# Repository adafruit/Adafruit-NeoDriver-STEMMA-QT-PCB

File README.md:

## Adafruit NeoDriver - I2C to NeoPixel Driver Board - Stemma QT PCB

<a href="http://www.adafruit.com/products/5766"><br/>
Click here to purchase one from the Adafruit shop</a>

PCB files for the Adafruit NeoDriver - I2C to NeoPixel Driver Board - Stemma QT. 

Format is EagleCAD schematic and board layout
* https://www.adafruit.com/product/5766

### Description

NeoPixel LEDs (a.k.a WS2812 / SK6812 family) are a super-easy way to add addressable RGB lighting with only one GPIO. They're ubiquitous on microcontrollers, but some chips or single board computers (SBCs) don't have neopixel support due to the precision timing required to send data.

We often get folks asking how to get NeoPixels working on some OrangeBananaOnionRockchipAllWinner Pi type board, given we have our Blinka library that provides support for CircuitPython libraries including the NeoPixel library. But if theres no neopixel_write implementation written for that platform, it just wont work. And writing the neopixel-writer function is non-trivial on many chips: you really need fast GPIO and nanosecond-perfect timing.

A quick solution is this seesaw-based NeoDriver board here: send it the NeoPixel data you want to write over I2C and it will blit out the perfect pixel timing on the other side. We're using an ATtiny1616 so we have enough RAM to buffer a 512-pixel long strand. now, to be fair - its not super fast because we have to write each pixel over I2C, but with a 800KHz or 1MHz I2C clock and as long as you're not writing the whole strip at once, its not so bad!

We add a 5V charge-pump so even on 3V boards, you'll get a clean 5V signal. The pre-soldered terminal blocks and Stemma QT plugs make this a no-solder solution for adding NeoPixels easily to any device with I2C. The default I2C address is 0x60 but you can cut the bottom solder traces to change it to 0x60-0x67 inclusive.

Please note: To power NeoPixels you'll need about 10-30mA per pixel of clean 5V DC power, provided on the terminal blocks or you can just wire the 5V directly to the pixels if there's separate red and black power wires. There's no way the Stemma QT port can provide that much current so you can't just wire the pixels without an external power supply!

### License

Adafruit invests time and resources providing this open source design, please support Adafruit and open-source hardware by purchasing products from [Adafruit](https://www.adafruit.com)!

Designed by Limor Fried/Ladyada for Adafruit Industries.

Creative Commons Attribution/Share-Alike, all text above must be included in any redistribution. 
See license.txt for additional details.

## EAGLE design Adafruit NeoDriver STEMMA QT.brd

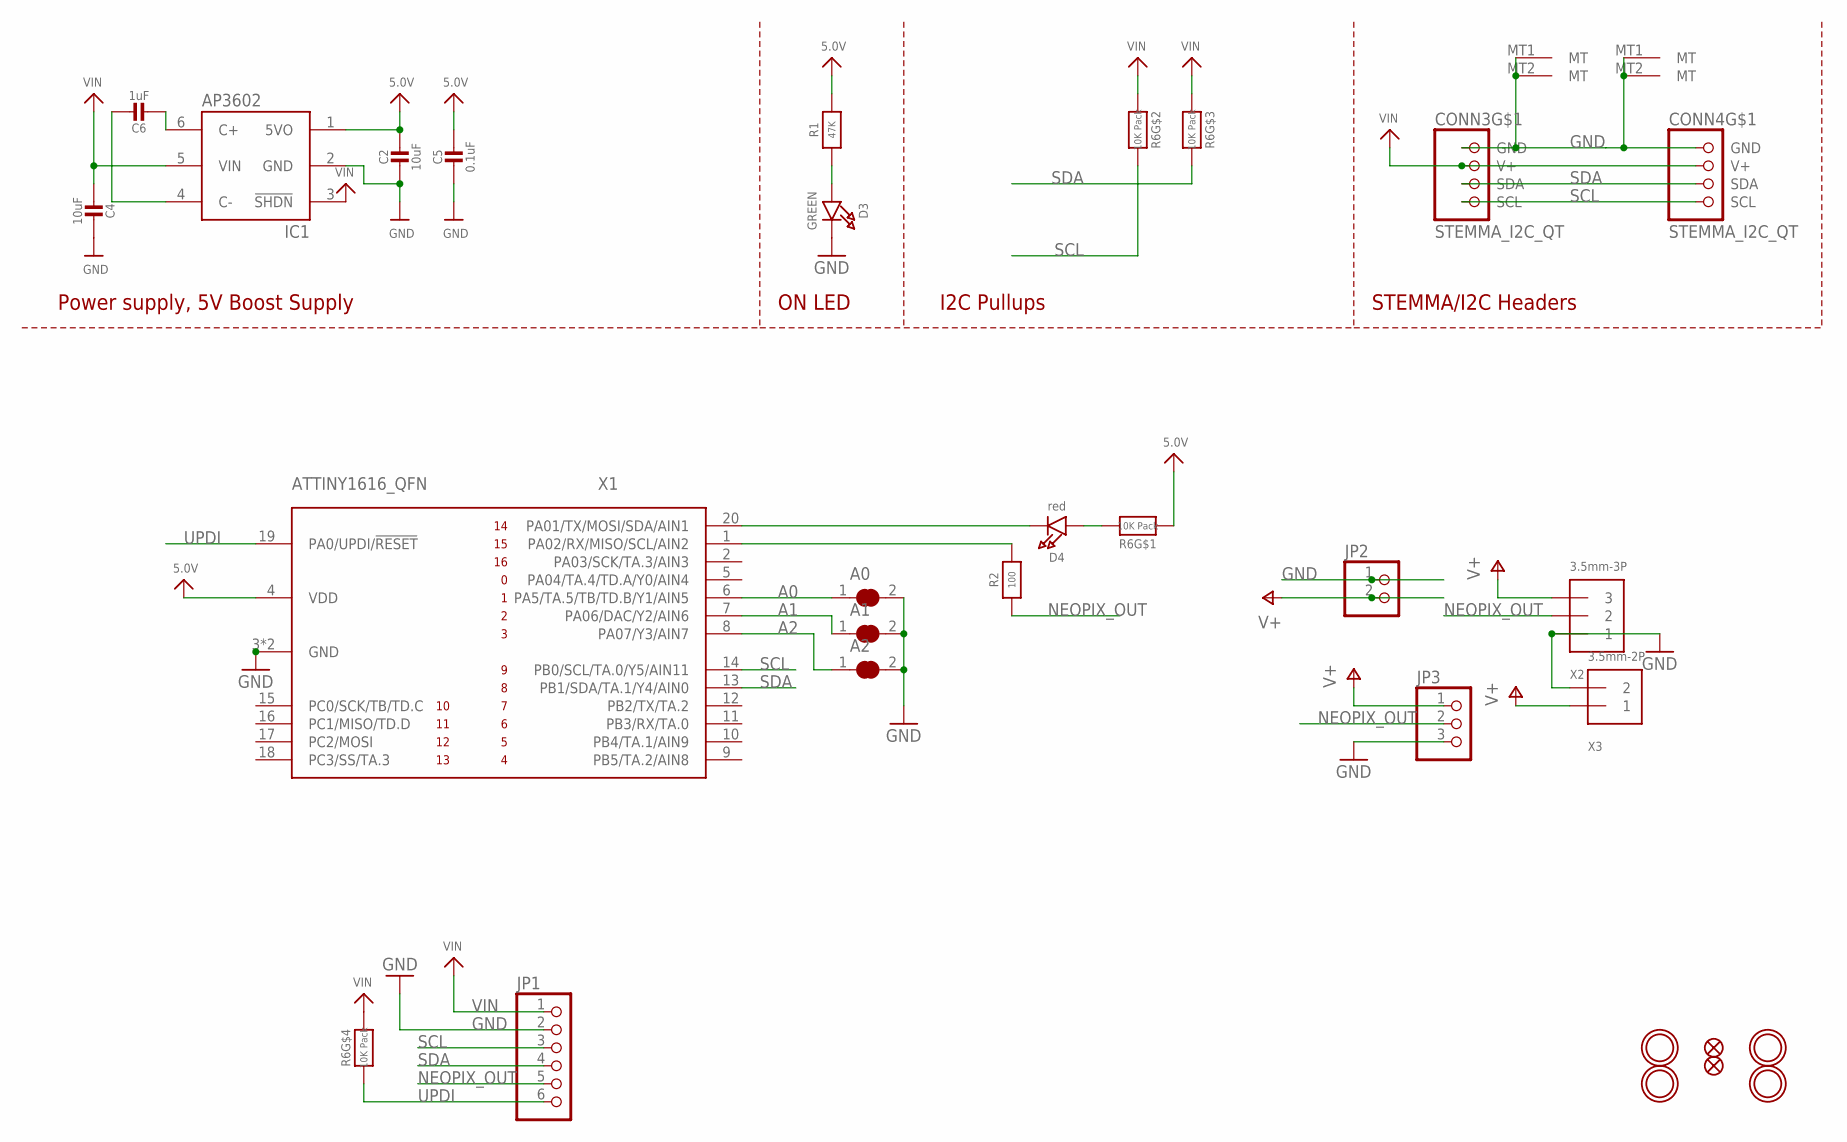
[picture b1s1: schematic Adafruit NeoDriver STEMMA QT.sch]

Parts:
A0, A1, A2: SOLDERJUMPER_CLOSED; SOLDERJUMPER_CLOSEDWIRE
C2, C4: 10uF; 0805-NO
C5: 0.1uF; 0603-NO
C6: 1uF; 0603-NO
CONN3, CONN4: STEMMA_I2C_QT; JST_SH4
D3: GREEN; CHIPLED_0603_NOOUTLINE
D4: red; CHIPLED_0603_NOOUTLINE
FID1, FID2: FIDUCIAL_1MM
IC1: AP3602; SOT23-6
JP1: HEADER-1X670MIL; 1X06_ROUND_70
JP2: HEADER-1X2ROUND; 1X02_ROUND
JP3: HEADER-1X3ROUND; 1X03_ROUND
R1: 47K; 0603-NO
R2: 100; 0603-NO
R6: 10K Pack; RESPACK_4X0603
U$1, U$6, U$9, U$18: MOUNTINGHOLE2.5; MOUNTINGHOLE_2.5_PLATED
X1: ATTINY1616_QFN; QFN20_3MM
X2: 3.5mm-3P; TERMBLOCK_1X3-3.5MM
X3: 3.5mm-2P; TERMBLOCK_1X2-3.5MM

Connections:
5.0V: C2.1, C5.1, IC1.1 (5VO), R1.2, R6.1, X1.4 (VDD)
A0: A0.1, X1.6 (PA5/TA.5/TB/TD.B/Y1/AIN5)
A1: A1.1, X1.7 (PA06/DAC/Y2/AIN6)
A2: A2.1, X1.8 (PA07/Y3/AIN7)
ACT: D4.C, X1.20 (PA01/TX/MOSI/SDA/AIN1)
GND: A0.2, A1.2, A2.2, C2.2, C4.2, C5.2, CONN3.1 (GND), CONN3.MT1 (MT), CONN3.MT2 (MT), CONN4.1 (GND), CONN4.MT1 (MT), CONN4.MT2 (MT), D3.C, IC1.2 (GND), JP1.2, JP2.1, JP3.3, X1.3 (GND), X1.PAD (GND), X2.1, X3.2
unnamed: D3.A, R1.1
unnamed: C6.2, IC1.6 (C+)
unnamed: C6.1, IC1.4 (C-)
unnamed: D4.A, R6.8 (2)
unnamed: R2.2, X1.1 (PA02/RX/MISO/SCL/AIN2)
NEOPIX_OUT: JP1.5, JP3.2, R2.1, X2.2
SCL: CONN3.4 (SCL), CONN4.4 (SCL), JP1.3, R6.7 (2), X1.14 (PB0/SCL/TA.0/Y5/AIN11)
SDA: CONN3.3 (SDA), CONN4.3 (SDA), JP1.4, R6.6 (2), X1.13 (PB1/SDA/TA.1/Y4/AIN0)
UPDI: JP1.6, R6.4 (1), X1.19 (PA0/UPDI/!RESET)
V+: JP2.2, JP3.1, X2.3, X3.1
VIN: C4.1, CONN3.2 (V+), CONN4.2 (V+), IC1.3 (!SHDN), IC1.5 (VIN), JP1.1, R6.2 (1), R6.3 (1), R6.5 (2)

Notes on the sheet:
I2C Pullups
STEMMA/I2C Headers
ON LED
Power supply, 5V Boost Supply

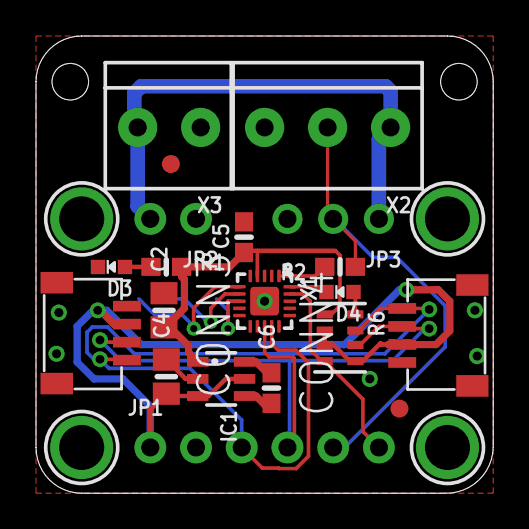
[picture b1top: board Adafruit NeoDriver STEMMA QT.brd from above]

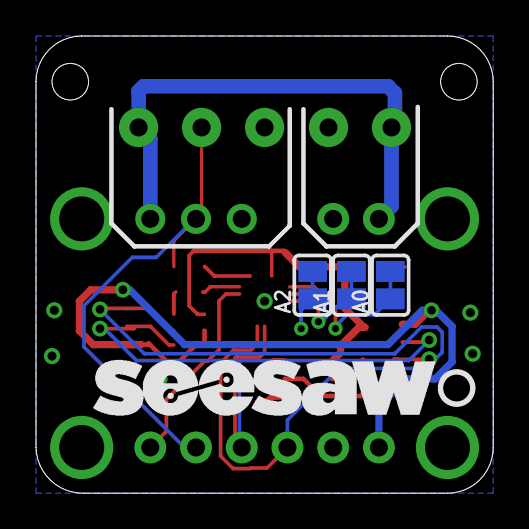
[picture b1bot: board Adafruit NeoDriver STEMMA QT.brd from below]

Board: 2 copper layers, 25.4 x 25.4 mm, 59 parts (17 on the bottom side), 17 nets.

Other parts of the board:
PLABEL0: PLABEL0
PLABEL1: PLABEL1
PLABEL2: PLABEL2
PLABEL3: PLABEL3
PLABEL4: PLABEL4
PLABEL5: PLABEL5
PLABEL6: PLABEL6
PLABEL7: PLABEL7
PLABEL8: PLABEL8
PLABEL9: PLABEL9
PLABEL10: PLABEL10
PLABEL11: PLABEL11
PLABEL12: PLABEL12
PLABEL13: PLABEL13
PLABEL14: PLABEL14
PLABEL15: PLABEL15
PLABEL16: PLABEL16
PLABEL17: PLABEL17
PLABEL18: PLABEL18
PLABEL19: PLABEL19
PLABEL20: PLABEL20
PLABEL21: PLABEL21
PLABEL22: PLABEL22
PLABEL23: PLABEL23
PLABEL24: PLABEL24
PLABEL25: PLABEL25
PLABEL26: PLABEL26
PLABEL27: PLABEL27
PLABEL28: PLABEL28
PLABEL29: PLABEL29
U$7: SEESAW_LOGO
U$12: PCBFEAT-REV-040

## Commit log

2023-06-05 adding cookiecutter output
2023-06-05 updating image

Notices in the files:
parts and their libraries:
microbuilder: This work is placed in the public domain, and may be freely used for commercial and non-commercial work with the following conditions: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
